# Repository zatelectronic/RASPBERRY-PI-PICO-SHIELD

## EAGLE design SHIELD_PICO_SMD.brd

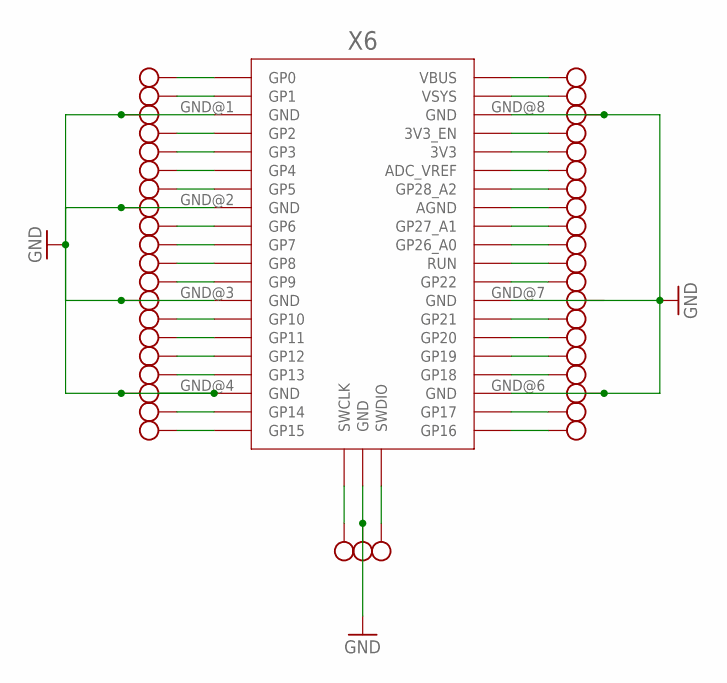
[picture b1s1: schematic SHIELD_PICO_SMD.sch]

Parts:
X1, X3: AK300/12
X2, X4: AK300/8
X5: AK300/3
X6: RPI_PICO_IG-SMD; RPI_PICO

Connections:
GND: X1.5, X1.10, X2.3, X2.8, X3.3, X4.1, X4.6, X5.2, X6.GND@1 (GND), X6.GND@2 (GND), X6.GND@3 (GND), X6.GND@4 (GND), X6.GND@5 (GND), X6.GND@6 (GND), X6.GND@7 (GND), X6.GND@8 (GND)
unnamed: X1.12, X6.GP0
unnamed: X1.11, X6.GP1
unnamed: X1.9, X6.GP2
unnamed: X1.8, X6.GP3
unnamed: X1.7, X6.GP4
unnamed: X1.6, X6.GP5
unnamed: X1.4, X6.GP6
unnamed: X1.3, X6.GP7
unnamed: X1.2, X6.GP8
unnamed: X1.1, X6.GP9
unnamed: X2.7, X6.GP10
unnamed: X2.6, X6.GP11
unnamed: X2.5, X6.GP12
unnamed: X2.4, X6.GP13
unnamed: X2.2, X6.GP14
unnamed: X2.1, X6.GP15
unnamed: X3.1, X6.VBUS
unnamed: X3.2, X6.VSYS
unnamed: X3.4, X6.3V3_EN
unnamed: X3.5, X6.3V3
unnamed: X3.6, X6.ADC_VREF
unnamed: X3.7, X6.GP28_A2
unnamed: X3.8, X6.AGND
unnamed: X3.9, X6.GP27_A1
unnamed: X3.10, X6.GP26_A0
unnamed: X3.11, X6.RUN
unnamed: X3.12, X6.GP22
unnamed: X4.2, X6.GP21
unnamed: X4.3, X6.GP20
unnamed: X4.4, X6.GP19
unnamed: X4.5, X6.GP18
unnamed: X4.7, X6.GP17
unnamed: X4.8, X6.GP16
unnamed: X5.3, X6.SWCLK
unnamed: X5.1, X6.SWDIO

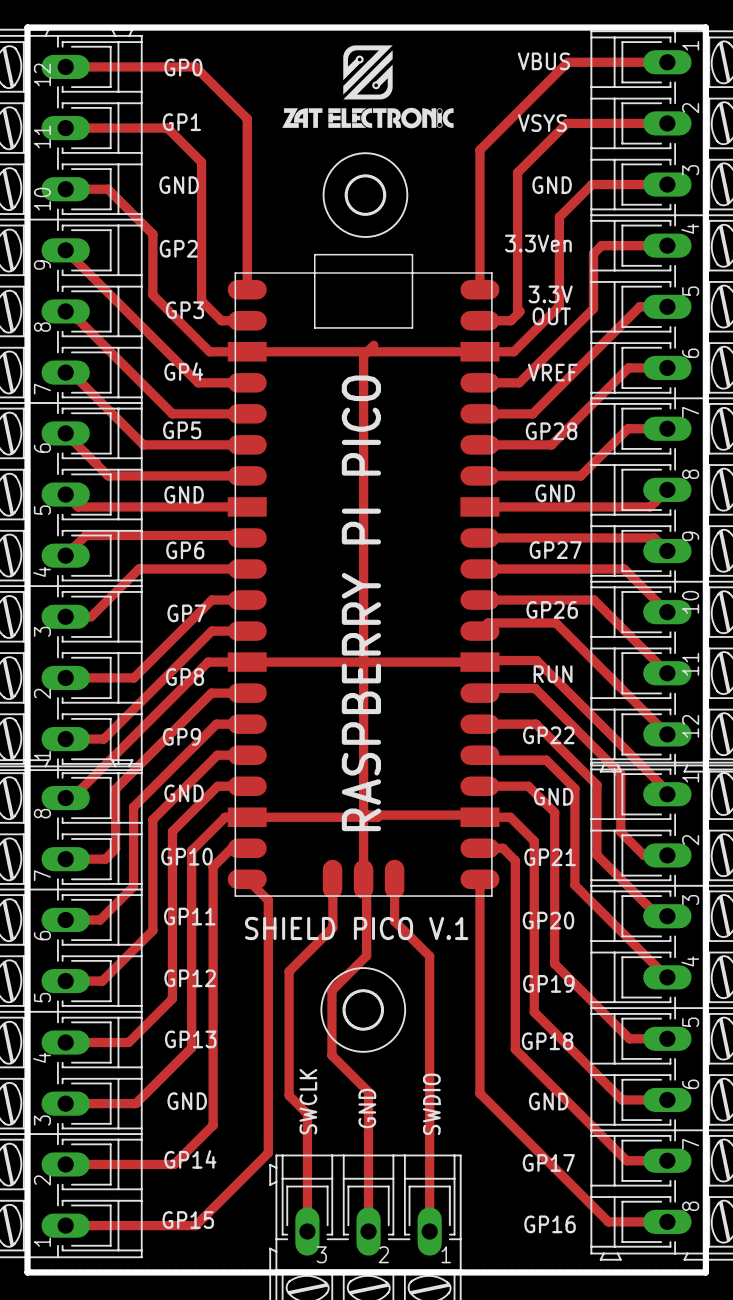
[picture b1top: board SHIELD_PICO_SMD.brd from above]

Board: 2 copper layers, 55.5 x 101.9 mm, 9 parts (0 on the bottom side), 36 nets.

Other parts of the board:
U$2, U$3: 3,0
U$4: LOGO_ESCRITA_MEDIO

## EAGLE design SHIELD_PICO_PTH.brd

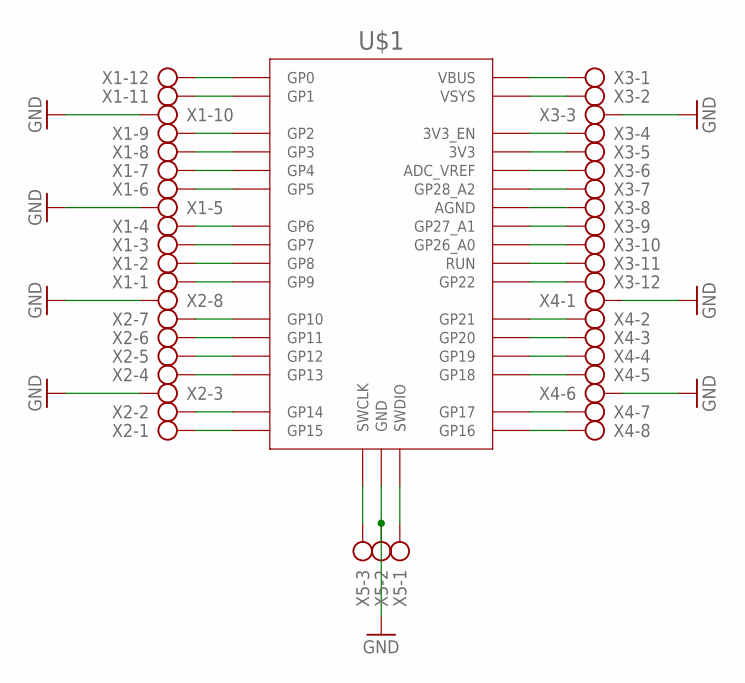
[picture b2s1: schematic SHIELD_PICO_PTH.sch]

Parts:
U$1: RPI_PICO-TH; RPI_PICO_TH
X1, X3: AK300/12
X2, X4: AK300/8
X5: AK300/3

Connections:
GND: U$1.GND@1 (GND), U$1.GND@2 (GND), U$1.GND@3 (GND), U$1.GND@4 (GND), U$1.GND@5 (GND), U$1.GND@6 (GND), U$1.GND@7 (GND), U$1.GND@8 (GND), X1.5, X1.10, X2.3, X2.8, X3.3, X4.1, X4.6, X5.2
unnamed: U$1.GP0, X1.12
unnamed: U$1.GP1, X1.11
unnamed: U$1.GP2, X1.9
unnamed: U$1.GP3, X1.8
unnamed: U$1.GP4, X1.7
unnamed: U$1.GP5, X1.6
unnamed: U$1.GP6, X1.4
unnamed: U$1.GP7, X1.3
unnamed: U$1.GP8, X1.2
unnamed: U$1.GP9, X1.1
unnamed: U$1.GP10, X2.7
unnamed: U$1.GP11, X2.6
unnamed: U$1.GP12, X2.5
unnamed: U$1.GP13, X2.4
unnamed: U$1.GP14, X2.2
unnamed: U$1.GP15, X2.1
unnamed: U$1.SWCLK, X5.3
unnamed: U$1.SWDIO, X5.1
unnamed: U$1.VBUS, X3.1
unnamed: U$1.VSYS, X3.2
unnamed: U$1.3V3_EN, X3.4
unnamed: U$1.3V3, X3.5
unnamed: U$1.ADC_VREF, X3.6
unnamed: U$1.GP28_A2, X3.7
unnamed: U$1.AGND, X3.8
unnamed: U$1.GP27_A1, X3.9
unnamed: U$1.GP26_A0, X3.10
unnamed: U$1.RUN, X3.11
unnamed: U$1.GP22, X3.12
unnamed: U$1.GP21, X4.2
unnamed: U$1.GP20, X4.3
unnamed: U$1.GP19, X4.4
unnamed: U$1.GP18, X4.5
unnamed: U$1.GP17, X4.7
unnamed: U$1.GP16, X4.8

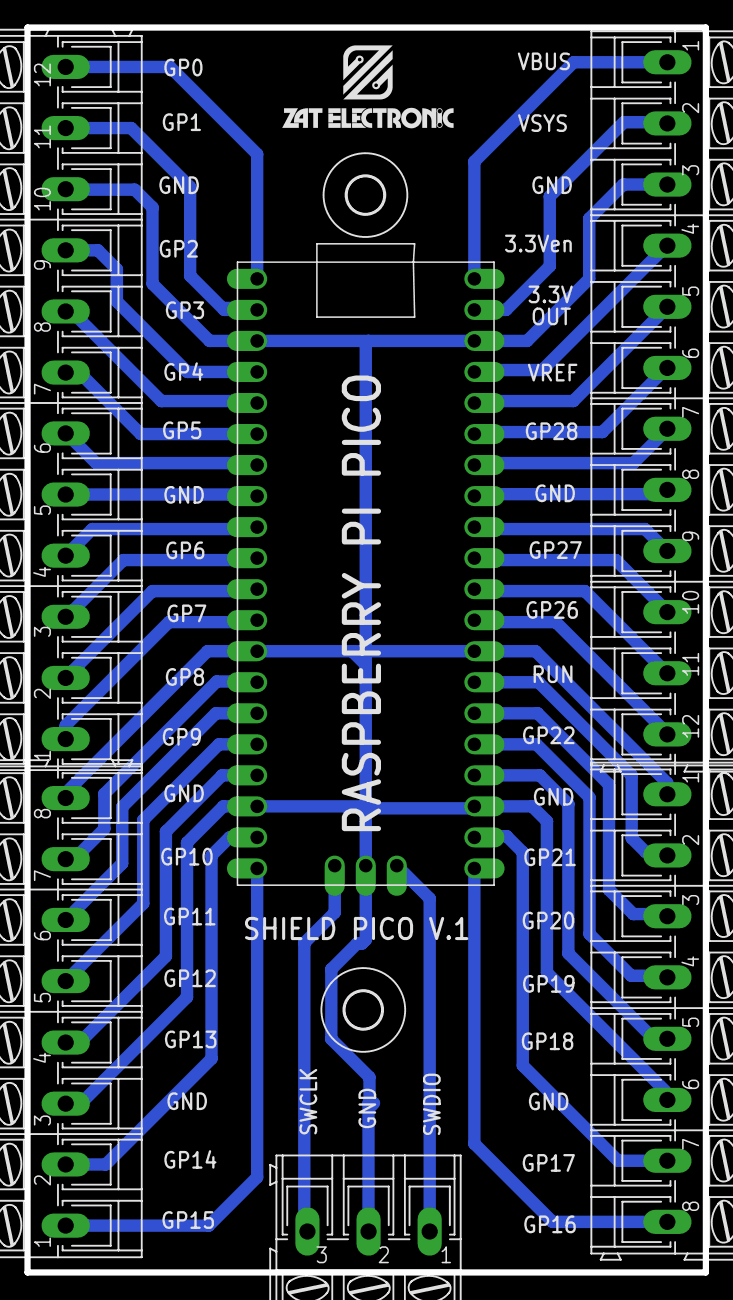
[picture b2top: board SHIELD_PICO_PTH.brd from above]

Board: 2 copper layers, 55.5 x 101.9 mm, 9 parts (0 on the bottom side), 36 nets.

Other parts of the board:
U$2, U$3: 3,0
U$4: LOGO_ESCRITA_MEDIO

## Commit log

2021-10-24 PRIMEIRO ENVIO
2021-10-25 ATUALIZAÇÃO
